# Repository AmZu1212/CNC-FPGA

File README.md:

# The FPGA Powered CNC Machine Project!

**Authors:** Amir Zuabi, Alexey Vassiliev
**Project Instructor:** Oz Shmueli

**Tech Stack:** Verilog HDL, Embedded C, AMD Vitis + Vivado 2024.2

FPGA-driven CNC / pen-plotter control system built around the AMD/Xilinx Zynq-7000
ZedBoard. The machine uses a ballpoint pen as its toolhead and draws 2D paths on
paper by coordinating X/Y motion and pen lift on the Z axis.

The project combines:

- real-time motion control in programmable logic
- SD-card file execution from embedded C software
- a custom PS/PL handshake for streaming toolpath data
- synchronized X/Y/Z stepping and homing behavior

## Project Extras
- [Project Book](https://docs.google.com/document/d/1OV_ynCNoAT1X2owSJ-zEwvw9sg0V5Sw3wNW-7_P0xBw/edit?usp=sharing)
- [Project Final Presentation](https://docs.google.com/presentation/d/1b78aWw7C5DXjPr4mND8HU1x7PuBJLt62-B5t3x_5M5w/edit?usp=sharing)
- [Project Poster](https://docs.google.com/presentation/d/1uY4deVW8epaZUn2_C40akR2pndnsqMq7fAAhxBZv-9M/edit?usp=sharing)

---

## Gallery

### The Finished Machine

### PCB / Electronics

### The Zedboard (Board Platform with PS/PL)

### System Overview

---

## What This Project Does

This project implements a complete CNC-style execution pipeline:

1. A `RUN.G` file is placed on an SD card
2. The Zynq PS mounts the SD card and reads the G-code
3. Embedded C software filters and converts supported motion commands
4. Motion data is written into AXI GPIO registers
5. The FPGA consumes commands and executes motion in hardware
6. The machine supports homing, start, cancel, return, and resumed runs

This is done using:

- Verilog RTL
- Vivado block design integration
- AXI register interfaces
- Embedded C firmware
- Vitis deployment flow

---

## Why It Is Technically Interesting

This project required work across several domains:

- **Digital design**
  Custom Verilog modules for command handling, motion coordination, handshaking, and driver control.

- **Embedded systems**
  C firmware for SD card access, G-code parsing, register writes, modal state handling, and PS/PL synchronization.

- **System integration**
  Vivado block design, AXI GPIO mapping, platform export, Vitis application flow, FPGA programming, and serial debugging.

- **Motion control**
  Coordinated X/Y/Z movement, homing, safe Z raises, speed handling, cancellation, and return-to-home logic.

- **Debugging and validation**
  Timing-sensitive PS/PL handshakes, startup behavior, stale register hazards, parsing corner cases, and hardware execution issues.

---

## Architecture

### PL Responsibilities

The programmable logic is responsible for deterministic motion execution:

- parser-side command sequencing
- motion coordination across X/Y/Z
- speed / timing translation into step generation
- homing and return behavior
- interaction with external stepper control logic

Key RTL modules include:

- `GCODE_Parser`
- `XYZ_Axis_Coordinator`
- `DriverController`

### PS Responsibilities

The processing system is responsible for file-driven command preparation:

- mounting the SD card
- opening `RUN.G`
- filtering G-code to supported motion commands (only G0/G1 are currently supported)
- converting units into machine format
- writing payload and handshake values into registers

---

## Supported G-code Behavior

The current software parser focuses on the motion subset needed for the machine workflow.

Supported behavior:

- accepts `G0` and `G1`
- ignores unsupported non-motion lines
- ignores comments
- preserves modal values for omitted `X`, `Y`, `Z`, and `F`
- converts:
    - `X/Y/Z`: mm -> microns
    - `F`: mm/min -> mm/s
- clamps motion values to the machine work area

Expected input file:

- SD card filename: `RUN.G`

---

## Repository Structure

- [`Zedboard-CNC/`](./Zedboard-CNC)
  Vivado hardware project, RTL, block design, and generated hardware artifacts.

- [`Vitis-Classic/`](./Vitis-Classic)
  Vitis Classic workspace and platform/application projects.

- [`Vitis3/`](./Vitis3)
  Vitis Classic workspace and platform/application projects. (the project is programmed to the board from here)

- [`Documentation/`](./Documentation)
  Sample G-code files, hex files, reference material, project assets, etc.

---

## How To Run

### Vivado

Use Vivado when you need to:

- inspect or edit the block design
- modify RTL
- regenerate the bitstream
- export hardware for Vitis (vitis needs an .xsa file, also, when exporting hardware, dont forget to include bitstream. without it yo ucannot program the PL side of things.)

### Vitis Classic

For normal use, the project should be launched directly from the existing Vitis Classic setup.

#### Step-by-step

1. Connect the board to the PC.
2. Connect the USB cable used for JTAG/programming.
3. Connect the USB cable used for UART/serial output.
4. Open the Vitis Classic workspace/project directory (Please note: open Vitis Classic, and not Vitis Unified).

6. Open the existing application project.
7. Make sure the board is powered.
8. Launch the application on hardware.(right click the project application, and press "launch on hardware")

10. Open the serial terminal if you want runtime prints.

For the normal checked-in working flow, no rebuild is required just to run the design if the workspace is already in a valid state.

### Serial Terminal

When using runtime prints:

- use the board UART COM port
- standard settings are typically:
    - `115200`
    - `8-N-1`
    - no flow control

---

## Wiring Guide

### Required Board Connections

- Zedboard power (i.e the included board power adapter)
- JTAG/programming USB
- UART USB
- SD card inserted (a micro-sd to SD adapter can be used and is recommended)

### Motion / Driver Wiring

The diagram above shows one complete motor assembly using the PMOD top `A`
cluster, an A4988 driver, a Nema 17 stepper motor, a limit switch, and a
12V-to-3.3V step-down supply. The same wiring pattern is reused for each axis.

Additional connections from the driver assembly:

- A4988 `2B`, `2A`, `1A`, `1B` connect to the Nema 17 motor phases.
- A4988 `VM` is powered from the `12V` supply.
- A4988 logic `VDD` is powered from the step-down `3.3V` output.
- All grounds must be common between the ZedBoard, step-down converter, driver, and power supply.
- A `100 uF` capacitor is placed across the motor supply near the A4988 driver.
- The PCB is designed for a `12V`, `3A` DC input supply.
- This can be provided either by a suitable wall power adapter or by a portable battery/power-bank setup, as used in this project, as long as it can reliably supply `12V` at `3A`.

The remaining PMOD clusters use the same signal order:

- PMOD `A`: X axis
- PMOD `B`: Z axis
- PMOD `C`: Y axis

The table below shows the shared signal order for all three PMOD motor clusters.

| Pin # | PMOD Pin Name | Signal Definition | A4988 / External Connection |
| ----- | ------------- | ----------------- | --------------------------- |
| `1` | `JA1 / JB1 / JC2_P` | `DIR` | A4988 `DIR` |
| `2` | `JA2 / JB2 / JC1_N` | `STEP` | A4988 `STEP` |
| `3` | `JA3 / JB3 / JC1_P` | `RST` | A4988 `RST` |
| `4` | `JA4 / JB4 / JC2_N` | `LSS` | Limit switch signal |
| `5` | `GND / GND / GND` | `LS-` | Limit switch return |
| `6` | `VCC / VCC / VCC` | `LS+` | Limit switch `V+` |
| `7` | `JA7 / JB7 / JC3_P` | `EN` | A4988 `EN` |
| `8` | `JA8 / JB8 / JC3_N` | `MS1` | A4988 `MS1` |
| `9` | `JA9 / JB9 / JC4_P` | `MS2` | A4988 `MS2` |
| `10` | `JA10 / JB10 / JC4_N` | `MS3` | A4988 `MS3` |
| `11` | `GND / GND / GND` | `GND` | A4988 `GND` / common ground |
| `12` | `VCC / VCC / VCC` | `SLP` | A4988 `SLP` / 3.3V logic rail |

### PS / PL Register Interface

The software and hardware communicate through AXI GPIO-backed registers.

The interface uses a small request/acknowledge handshake between the Processing
System (PS) and Programmable Logic (PL). The PL raises `MOUNT_REQ` when it wants
the PS to open and prepare a job. The PS answers with `MOUNT_OK` or `MOUNT_FAIL`.
After that, the PL requests the next motion entry by changing `REQ`. The PS writes
`X`, `Y`, `Z`, `SPEED`, and `LAST_LINE`, then updates `ACK` to the same phase only
after the data is ready. Matching `REQ` and `ACK` tells the PL that the next
motion command is valid and can be executed.

| Direction | Register Name | Purpose |
| --------- | ------------- | ------- |
| PS → PL | `X` | Next command X position written by the C application. |
| PS → PL | `Y` | Next command Y position written by the C application. |
| PS → PL | `Z` | Next command Z position written by the C application. |
| PS → PL | `SPEED` | Speed value associated with the current motion command. |
| PS → PL | `ACK` | Phase acknowledge register. Updated only after the new command data is valid. |
| PS → PL | `MOUNT_OK` | Indicates that the PS mounted the SD card and opened the job successfully. |
| PS → PL | `MOUNT_FAIL` | Indicates that the PS could not mount or open the requested job. |
| PS → PL | `LAST_LINE` | Marks that the currently served motion command is the final valid line in the file. |
| PL → PS | `REQ` | Phase request register used by the PL to ask for the next motion command. |
| PL → PS | `MOUNT_REQ` | Session request bit used by the PL to tell the PS to mount and prepare a file. |

---

## Typical Runtime Flow

1. PS detects a mount request from the PL
2. PS mounts the SD card and opens `RUN.G`
3. PS preloads the first valid motion command
4. PL acknowledges and advances through phase-based requests
5. PS serves one motion at a time through AXI registers
6. PL executes the path in hardware
7. On cancel, the machine performs a controlled return-to-home sequence

---

## Current Status

The system demonstrates a working end-to-end CNC control path:

- SD card file loading
- C-based G-code parsing and conversion
- PS/PL handshake and register streaming
- hardware motion execution
- homing, start, cancel, and restart behavior

This repository represents substantial work in:

- FPGA design
- embedded software
- control logic
- hardware/software integration
- debugging of real machine behavior

---

## Notes

- `RUN.G` is the expected job filename on the SD card
- some folders contain bring-up code and experiments in addition to the main working flow
- platform regeneration may be required when hardware-visible interfaces change

---

## Authors

A Project by Amir Zuabi & Alex Vassiliev

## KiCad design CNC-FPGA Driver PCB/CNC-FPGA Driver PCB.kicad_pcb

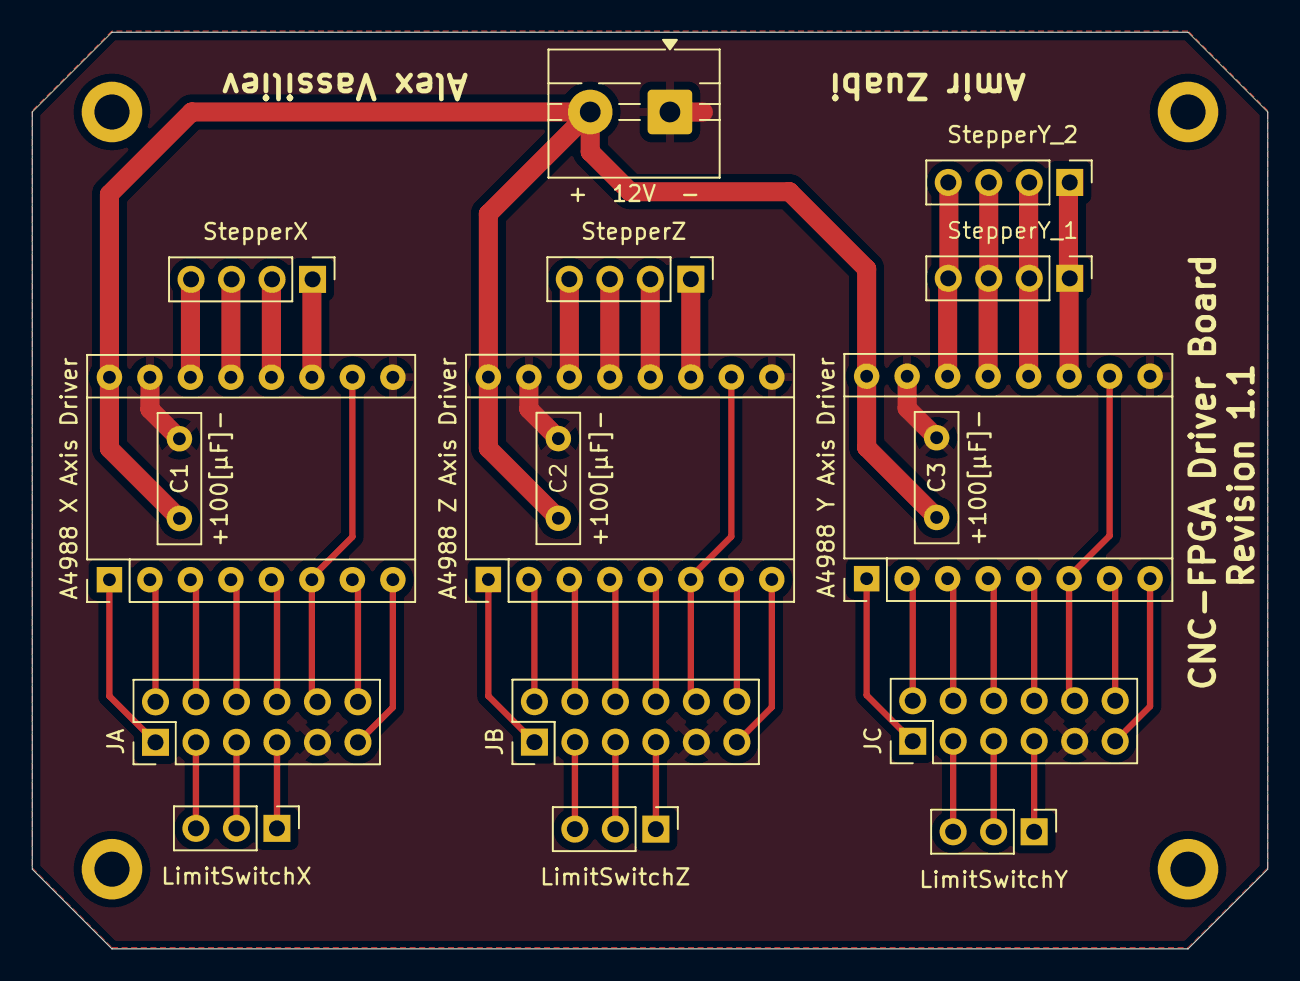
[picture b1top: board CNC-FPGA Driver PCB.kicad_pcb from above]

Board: 2 copper layers, 77.5 x 57.5 mm, 17 parts (0 on the bottom side), 18 nets.

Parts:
+100[µF]-: C3; C_Disc_D8.0mm_W2.5mm_P5.00mm
+100[µF]-#2: C2; C_Disc_D8.0mm_W2.5mm_P5.00mm
+  12V  - : 12V_Screw_Terminal; TerminalBlock_MaiXu_MX126-5.0-02P_1x02_P5.00mm
A4988 X Axis Driver: A4988 N Axis Driver; Pololu_Breakout-16_15.2x20.3mm
A4988 Y Axis Driver, A4988 Z Axis Driver: A4988 Stepper Driver; Pololu_Breakout-16_15.2x20.3mm
C1: +100[µF]-; C_Disc_D8.0mm_W2.5mm_P5.00mm
JA: 2x6 DuPont PMOD; PinHeader_2x06_P2.54mm_Vertical
JB: 2x6 DuPont PMOD; PinHeader_2x06_P2.54mm_Vertical
JC: 2x6 DuPont PMOD; PinHeader_2x06_P2.54mm_Vertical
LimitSwitchX: Axis; PinHeader_1x03_P2.54mm_Vertical
LimitSwitchY: Axis; PinHeader_1x03_P2.54mm_Vertical
LimitSwitchZ: Axis; PinHeader_1x03_P2.54mm_Vertical
StepperX: DuPont 1x4; PinHeader_1x04_P2.54mm_Vertical
StepperY_1, StepperY_2: DuPont 1x4; PinHeader_1x04_P2.54mm_Vertical
StepperZ: DuPont 1x4; PinHeader_1x04_P2.54mm_Vertical

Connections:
+3.3V: A4988 X Axis Driver.10 (VDD), A4988 Y Axis Driver.10 (MS1), A4988 Z Axis Driver.10 (MS1)
/DIR: A4988 X Axis Driver.8 (DIR), A4988 Y Axis Driver.8 (VMOT), A4988 Z Axis Driver.8 (VMOT), JA.12 (Pin_1), JB.12 (Pin_11), JC.12 (Pin_11)
/EN: A4988 X Axis Driver.1 (~ENABLE), A4988 Y Axis Driver.1 (GND), A4988 Z Axis Driver.1 (GND), JA.7, JB.7 (Pin_1), JC.7 (Pin_1)
/LS+: JA.10 (Pin_6), JB.10 (Pin_7), JC.10 (Pin_7), LimitSwitchX.1 (C), LimitSwitchY.1 (C), LimitSwitchZ.1 (C)
/LS-: JA.8 (Pin_5), JB.8 (Pin_3), JC.8 (Pin_3), LimitSwitchX.3 (A), LimitSwitchY.3 (A), LimitSwitchZ.3 (A)
/LSS: JA.9 (Pin_4), JB.9 (Pin_5), JC.9 (Pin_5), LimitSwitchX.2 (B), LimitSwitchY.2 (B), LimitSwitchZ.2 (B)
/MS1: A4988 X Axis Driver.2 (MS1), A4988 Y Axis Driver.2 (VDD), A4988 Z Axis Driver.2 (VDD), JB.1 (Pin_2), JC.1 (Pin_2)
/MS2: A4988 X Axis Driver.3 (MS2), A4988 Y Axis Driver.3 (1B), A4988 Z Axis Driver.3 (1B), JA.2 (Pin_9), JB.2 (Pin_4), JC.2 (Pin_4)
/MS3: A4988 X Axis Driver.4 (MS3), A4988 Y Axis Driver.4 (1A), A4988 Z Axis Driver.4 (1A), JA.3 (Pin_10), JB.3 (Pin_6), JC.3 (Pin_6)
/RST: A4988 X Axis Driver.5 (~RESET), A4988 Y Axis Driver.5 (2A), A4988 Z Axis Driver.5 (2A), JA.4 (Pin_3), JB.4 (Pin_8), JC.4 (Pin_8)
/SLP: A4988 X Axis Driver.6 (~SLEEP), A4988 Y Axis Driver.6 (2B), A4988 Z Axis Driver.6 (2B), JA.5 (Pin_12), JB.5 (Pin_10), JC.5 (Pin_10)
/STEP: A4988 X Axis Driver.7 (STEP), A4988 Y Axis Driver.7 (GND), A4988 Z Axis Driver.7 (GND), JA.6 (Pin_2), JB.6 (Pin_12), JC.6 (Pin_12)
GND: +100[µF]-.2, +100[µF]-#2.2, + 12V -.1 (Pin_2), A4988 X Axis Driver.9 (GND), A4988 X Axis Driver.15 (GND), A4988 Y Axis Driver.9 (~ENABLE), A4988 Y Axis Driver.15 (STEP), A4988 Z Axis Driver.9 (~ENABLE), A4988 Z Axis Driver.15 (STEP), C1.2, JA.11, JB.11 (Pin_9), JC.11 (Pin_9)
unnamed: A4988 X Axis Driver.12 (1A), A4988 Y Axis Driver.12 (MS3), A4988 Z Axis Driver.12 (MS3), StepperX.2, StepperY_1.2, StepperY_2.2, StepperZ.2
unnamed: A4988 X Axis Driver.11 (1B), A4988 Y Axis Driver.11 (MS2), A4988 Z Axis Driver.11 (MS2), StepperX.1, StepperY_1.1, StepperY_2.1, StepperZ.1
unnamed: A4988 X Axis Driver.13 (2A), A4988 Y Axis Driver.13 (~RESET), A4988 Z Axis Driver.13 (~RESET), StepperX.3, StepperY_1.3, StepperY_2.3, StepperZ.3
unnamed: A4988 X Axis Driver.14 (2B), A4988 Y Axis Driver.14 (~SLEEP), A4988 Z Axis Driver.14 (~SLEEP), StepperX.4, StepperY_1.4, StepperY_2.4, StepperZ.4
unnamed: +100[µF]-.1, +100[µF]-#2.1, + 12V -.2 (Pin_1), A4988 X Axis Driver.16 (VMOT), A4988 Y Axis Driver.16 (DIR), A4988 Z Axis Driver.16 (DIR), C1.1

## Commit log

2025-05-28 platofrmIO Init
2025-05-28 esp stepper test code
2025-06-06 added sopc pdf tutorial
2025-06-11 AMD Projects upload.
2025-06-11 documentation upload
2025-06-11 folder reordering
2025-06-12 starter verilog IO driver
2025-06-17 opened new official cnc project, moved old design int oa block diagram properly.
2025-06-19 Repo Cleanup
2025-06-19 not sure, some update
2025-06-19 test commit
2025-06-19 Clean up
2025-06-22 XYZ Axis Coordinator + start of GCODE Parser + block diagram
2025-06-24 Adding v1.0 of PCB Design
2025-06-24 updated pcb traces
2025-06-24 added M2 mounting holes to pcb
2025-06-25 fixed timing but still working on constraints
2025-06-25 some pcb improvements, text & cut corners
2025-06-26 resolved software timing issue
2025-09-21 attempt #1 at solving enable pin logic
2025-09-26 pcb updated to fit 2 motors on Z axis
2025-09-26 First refactor into StateMachine
2025-10-19 Refactoring to State Machine
2025-11-30 added Y & Z axis ports
2025-12-24 added PS<->PL Demo project, will be expanded to SD card reading.
2025-12-24 added SD<->PS<->PL Reading demo
2025-12-25 adjusted steps/mm for belts vs lead screw
2025-12-25 finished baseline C SD slave + reordering + compiler options
2025-12-25 added python gcode sanitizer
2025-12-25 added proper gcode parsing
2025-12-25 added proper Gcode parsing, added missign speed register
2026-01-22 fixed axis scaling + bug known with speed
2026-02-21 added manual adjust, removed redundant checks
2026-02-25 added verilog testing folder with an exec script.
2026-02-25 testing script simplification + cleanup
2026-02-25 added iterative division block
2026-02-25 added testing outputs to gitignore
2026-02-25 verilog updates
2026-02-25 latest coordinator
2026-03-02 fixed speed bug and added run cancel functionality
2026-03-03 new speed method
2026-03-03 added button homing :)
2026-03-03 bitstream updated to current.
2026-03-03 Project Clean-up + Re-order
2026-03-03 more re-ordering
2026-03-04 added input hexfiles
2026-03-04 hex file re-order
2026-03-04 design strategy change (Flow_Quick)
2026-03-04 removed redundant comments
2026-03-04 added gcode parser to verilog library
2026-03-04 decoupled memory from parser.
2026-03-04 small bugfix to the parser.
2026-03-05 added registers
2026-03-05 added c templates
2026-03-05 sd demo update
2026-03-06 moved some files to docs
2026-03-06 added vitis classic repo
2026-03-06 renamed register in sd demo
2026-03-06 re ordered sd example project
2026-03-06 last example update
2026-03-06 fixed sd card pin wire
2026-03-06 sd read demo fixed
2026-03-06 cleanup
2026-03-06 switch z xis switch due to hardware failure
2026-03-06 platform updates
2026-03-06 plat chng2
2026-03-08 reset hardware to working order.
2026-03-09 cleanup + reset to minimal working
2026-03-09 added mounting signals
2026-03-09 added new GPIO registers.
2026-03-09 saving working hardware modules.
2026-03-09 connected ps registers + tested working
2026-03-09 added C code mount + led working test
2026-03-09 added missing mount_request bit
2026-03-09 updated to final platform
2026-03-09 added basic c version. some known bugs.
2026-03-09 added hardware signals for EOF + an almost working C version
2026-03-09 fixed race conditions + homing bug.
2026-03-09 FINAL C VERSION UPLOAD
2026-03-09 added axis clamping to 0-190mm
2026-03-11 uploaded machine 3d model
2026-03-11 cleaned up documentation folder
2026-03-11 added verilog library to gitignore
2026-03-11 moved sd example project to documentation folder
2026-03-11 removed old example folder
2026-03-18 documentation renames
2026-03-18 cleaned up block diagram. fixed axis naming inconsistency issues
2026-03-18 Added doxygen comments to C file
2026-03-19 re-added test hexfiles
2026-03-19 updated 3d model & added multicycle definitions
2026-03-19 last tech push before submission
2026-03-19 updated the PCB revision
2026-03-19 added a basic template readme
2026-03-19 Enhance README with tech stack and image updates
    Added tech stack information and updated image captions.
2026-03-19 Add image to README for machine photo
    added banner image
2026-03-19 changed step guide order
2026-03-19 added images to vitis flow
    Reordered steps for clarity and added images for each step.
2026-03-19 fixed identation issue
    Added an image of the machine to the README.
2026-03-19 Update tech stack version in README
    Updated tech stack to include version 2024.2.
2026-03-19 Add system overview section to README
    Added a section for system overview with an image.
2026-03-19 Add wiring diagram image to README
    Added an image to the Motion / Driver Wiring section.
2026-03-19 updated motor wiring section
2026-03-19 Clarify hardware/software control stack in README
    Updated the README to clarify the hardware/software control stack and its components.
2026-03-19 re-typed the pl ps register section
2026-03-19 Add machine flow image to README
    Added an image to illustrate the machine flow.
2026-03-19 Add image for responsibilities in README
    Added an image to illustrate responsibilities in the README.
2026-03-19 Add top banner image to README
2026-03-19 Add bottom banner image to README
2026-03-19 Update project title in README
2026-03-19 Remove demo video instructions from README
    Removed demo video section from README.
2026-03-26 added 3d prints stl's
2026-03-27 added project docs to readme
2026-03-30 added hotfix to over/under stepping
2026-03-30 added entry to gitignore
2026-03-30 updated hardware + software to the new hotfix
2026-04-19 last cleanup
2026-04-26 created and added BOOT.bin for boot programming
2026-04-26 added sd backup to doc folder + cleanup
2026-04-26 removed packages folder
